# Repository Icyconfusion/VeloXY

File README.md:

# VeloXY
A CoreXY 3d printer with a heated chamber and bed. It has 300x300x320 print volume and 3 point bed-levelling. I made this project to be able to print higher quality materials. The printer runs Marlin firmware.

## **Assembly**
The assembly is centered around a frame made of galvanised square steel (40x40). The frame is essentially a cube, where the square steel is welded together, so no connectors are needed. Two cross bars at the top are lowered by ~60mm to provide clearance for the extruder and filament path. 

Components are mounted onto the square steel using rivet nuts. 

### Z axis

The Z axis uses 3 independent motors to enable 3 point bed-levelling. At each motor, there is a T8 leadscrew to drive motion, and an 8mm smooth rod for support. The smooth rod is press fit into the 3d printed brackets through small slits in the brackets for compliance. The nema 17 motor mounts to the bracket, and secures the leadscrew with a 5x8 shaft coupler. At the idler, the leadscrew is held in place with a 16x8x5 bearing, allowing rotation. 

The intersection of the corner Nema 17 motors with the square steel is not an error, as a section of the square steel will be cutout (a rectangle just bigger than the motor) so that the motor sits in there without touching any of the steel.

Bed supports hold an LM8UU bearing and a anti-backlash nut. This transfers motion to the bed. The bed sits on these supports through a threaded steel ball (Vcore system) which rests on metal dowels in the bracket.

### Gantry (X and Y)
The gantry is the 2020 T slot profile that moves back and forth along the Y axis. The gantry is supported by two 3d printed brackets, one at each end, that connect it to the MGN12H carriages. The Y linear rails are mounted on the underside of the frame.

 The gantry has a linear rail along the top face of the profile, this is the X axis.

The extruder runs along this linear rail for the X axis. The extruder is sat on a MGN12H carriage, and holds a nema 17 motor for the extruder and the hotend. Two blower fans cool the nozzle/part.

### Chamber
The chamber is mounted around the frame, aiming to create a closed off area that can be heated for better printing. The enclosure is made up of ACM, mounted on the top, back, bottom and sides using rivet nuts.

A hole is drilled in the back panel so that wires for electronics can enter the chamber.

The enclosure is finished with a polycarbonate door on a hinge mounted to the frame, with a 3d printed handle.

The chamber is heated by a PTC heater in the bottom corner, mounted to a base tube of square steel, and a vertical post using a small metal rectangle with mounting holes drilled.

### Motion
The printer is based on a coreXY motion system. The belts are stacked on top of each other, so there is no need for a crossover system.

There are pulleys on the idlers and belt post on the gantry. The belts connect to a post/screw on the extruder.

## **Electronics**
I designed a PCB motherboard around the mega2560 that will control the printer. The motherboard is 2 layers and uses A4988 footprint drivers. Power for the motors and heaters enters the board with a screw terminal from the 24v 600w PSU. There is also an 5v screw terminal input which powers the motor driver logic, lcd and if needed the arduino. The 5v comes from the psu but with a buck converter between. There is a third power input for the arduino vin pin which can be used if needed, but the arduino can also be powered by the 5v supply and usb. The LCD connects to a 4 pin header, with RX, TX, 5V and GND. All three heaters (Hotend, bed and chamber) are controlled through TO-220 mosfets, but the chamber has its own PSU. There are also fuses for the power inputs.

## **BOM**
**Printed parts**
| Part | Quantity | Picture |
|------|----------|---------|
| A bottom corner | 1 |
| A bed support | 1 | 
| A idler | 1 |
| A motor | 1 | 
| A gantry belt post | 1 |
| A gantry mount | 1 | 
| B bottom corner | 1 | 
| B bed support | 1 |
| B idler | 1 | 
| B motor | 1 | 
| B gantry belt post | 1 | 
| B gantry mount | 1 | 
| Z front bracket | 1 |
| Front bed support | 1 | 
| Front top support | 1 | 
| Handle | 1 | 
| Extruder | 1 | 
| Electronics case | 1 | 

**Purchased Parts**
|Name             |Purpose                                                                                                                                                                                                                                |Quantity|Total Cost (USD)|Link                                                                                                                                                                                                                                                                                                                                                                                                                                                                                                                                                                                                                                                                                                                                                                                   |Distributor       |
|-----------------|---------------------------------------------------------------------------------------------------------------------------------------------------------------------------------------------------------------------------------------|--------|----------------|---------------------------------------------------------------------------------------------------------------------------------------------------------------------------------------------------------------------------------------------------------------------------------------------------------------------------------------------------------------------------------------------------------------------------------------------------------------------------------------------------------------------------------------------------------------------------------------------------------------------------------------------------------------------------------------------------------------------------------------------------------------------------------------|------------------|
|Mosfets          |IRLB3034PBF MOSFETs for controlling the heaters of the printer.                                                                                                                                                                        |3       |4.06            |https://www.aliexpress.com/item/4000222160431.html?spm=a2g0o.productlist.main.1.701d2eacHI2noh&algo_pvid=e8668151-e46e-4309-800e-2077e72375df&algo_exp_id=e8668151-e46e-4309-800e-2077e72375df-0&pdp_ext_f=%7B%22order%22%3A%2266%22%2C%22spu_best_type%22%3A%22price%22%2C%22eval%22%3A%221%22%2C%22fromPage%22%3A%22search%22%7D&pdp_npi=6%40dis%21AUD%215.88%211.45%21%21%214.00%210.98%21%40210328c017752737169366011ebd3e%2110000000864172031%21sea%21AU%216973160092%21ABX%211%210%21n_tag%3A-29910%3Bd%3A6fbdfe4b%3Bm03_new_user%3A-29895%3BpisId%3A5000000197843419&curPageLogUid=LSIIE8dqceVT&utparam-url=scene%3Asearch%7Cquery_from%3A%7Cx_object_id%3A4000222160431%7C_p_origin_prod%3A                                                                                    |Aliexpress        |
|Capacitors       |220 uf 50V capacitors for the motherboard                                                                                                                                                                                              |6       |3.80            |https://www.aliexpress.com/item/1005011631970768.html?spm=a2g0o.productlist.main.6.11e01afbH7otWg&algo_pvid=ea0e70cf-552e-4c24-aa21-9a0a49e67bf6&algo_exp_id=ea0e70cf-552e-4c24-aa21-9a0a49e67bf6-5&pdp_ext_f=%7B%22order%22%3A%22889%22%2C%22eval%22%3A%221%22%2C%22fromPage%22%3A%22search%22%7D&pdp_npi=6%40dis%21AUD%212.71%211.45%21%21%2112.71%216.80%21%4021030a6217752717653413118ea4b9%2112000056427936714%21sea%21AU%216973160092%21ABX%211%210%21n_tag%3A-29910%3Bd%3A6fbdfe4b%3Bm03_new_user%3A-29895%3BpisId%3A5000000197843456&curPageLogUid=3mj5Ipi5ZoII&utparam-url=scene%3Asearch%7Cquery_from%3A%7Cx_object_id%3A1005011631970768%7C_p_origin_prod%3A                                                                                                                |Aliexpress        |
|female headers   |For connecting the A4988 drivers to the motherboard                                                                                                                                                                                    |12      |5.52            |https://www.aliexpress.com/item/4000059515638.html?spm=a2g0o.productlist.main.9.3a78pSyIpSyIFy&algo_pvid=1a6644c9-0d15-4e98-a974-f6610573b0b1&algo_exp_id=1a6644c9-0d15-4e98-a974-f6610573b0b1-8&pdp_ext_f=%7B%22order%22%3A%22284%22%2C%22eval%22%3A%221%22%2C%22fromPage%22%3A%22search%22%7D&pdp_npi=6%40dis%21AUD%2114.21%211.45%21%21%219.67%210.98%21%402101c44517752688612072065e0933%2112000028027640857%21sea%21AU%216973160092%21ABX%211%210%21n_tag%3A-29910%3Bd%3A6fbdfe4b%3Bm03_new_user%3A-29895%3BpisId%3A5000000197843419&curPageLogUid=7JxZIhsilBI0&utparam-url=scene%3Asearch%7Cquery_from%3A%7Cx_object_id%3A4000059515638%7C_p_origin_prod%3A                                                                                                                      |Aliexpress        |
|Male pin headers |For connecting components like endstops and the MCU to the motherboard                                                                                                                                                                 |1       |8.74            |https://www.aliexpress.com/item/1005011692961056.html?spm=a2g0o.productlist.main.6.57f6487bkxhM2t&algo_pvid=cf18d2a9-385d-4fc5-8ad6-75333b3f4af1&algo_exp_id=cf18d2a9-385d-4fc5-8ad6-75333b3f4af1-5&pdp_ext_f=%7B%22order%22%3A%221274%22%2C%22eval%22%3A%221%22%2C%22orig_sl_item_id%22%3A%221005011692961056%22%2C%22orig_item_id%22%3A%221005010337310648%22%2C%22fromPage%22%3A%22search%22%7D&pdp_npi=6%40dis%21AUD%217.68%211.45%21%21%2136.00%216.80%21%40210319b717752687310407356e8479%2112000056260706301%21sea%21AU%216973160092%21ABX%211%210%21n_tag%3A-29910%3Bd%3A6fbdfe4b%3Bm03_new_user%3A-29895%3BpisId%3A5000000197843456&curPageLogUid=2ZVKkz74AUod&utparam-url=scene%3Asearch%7Cquery_from%3A%7Cx_object_id%3A1005011692961056%7C_p_origin_prod%3A1005010337310648|Aliexpress        |
|Blower fan       |Cooling the nozzle/part                                                                                                                                                                                                                |2       |4.60            |https://www.aliexpress.com/item/1005006744255466.html?spm=a2g0o.productlist.main.18.7f9f5db3RONGTo&aem_p4p_detail=202604031902574206037527561500000981548&algo_pvid=619f652d-2eee-4128-aee8-e13ab89bcbb5&algo_exp_id=619f652d-2eee-4128-aee8-e13ab89bcbb5-15&pdp_ext_f=%7B%22order%22%3A%2233%22%2C%22eval%22%3A%221%22%2C%22fromPage%22%3A%22search%22%7D&pdp_npi=6%40dis%21AUD%216.67%216.29%21%21%2131.26%2129.48%21%402103274e17752681771328222e87ef%2112000056790491158%21sea%21AU%216973160092%21ABX%211%210%21n_tag%3A-29910%3Bd%3A6fbdfe4b%3Bm03_new_user%3A-29895&curPageLogUid=7c9OwehxviKo&utparam-url=scene%3Asearch%7Cquery_from%3A%7Cx_object_id%3A1005006744255466%7C_p_origin_prod%3A&search_p4p_id=202604031902574206037527561500000981548_4                          |Aliexpress        |
|Bearing          |16x8x5 bearing for holding the top of leadscrews in place                                                                                                                                                                              |3       |0.45            |https://jlcmc.com/product/b/C15/BR8364/deep-groove-ball-bearing-double-side-with-dust-cover                                                                                                                                                                                                                                                                                                                                                                                                                                                                                                                                                                                                                                                                                            |JLCMC             |
|Fuse             |KCD3 Fuse holder for the motherboard. For the main PSU, 30-35A fuse. For bed PSU, 20A fuse.                                                                                                                                            |2       |7.80            |https://www.aliexpress.com/item/1005005182079397.html?spm=a2g0o.productlist.main.37.46d42d7bflqGAT&algo_pvid=e277db1d-0a25-4cd8-b4e5-8a226238a0aa&algo_exp_id=e277db1d-0a25-4cd8-b4e5-8a226238a0aa-36&pdp_ext_f=%7B%22order%22%3A%22680%22%2C%22eval%22%3A%221%22%2C%22fromPage%22%3A%22search%22%7D&pdp_npi=6%40dis%21AUD%215.28%211.45%21%21%2124.76%216.81%21%402101e2b017752723764397683ed113%2112000040889150142%21sea%21AU%216973160092%21ABX%211%210%21n_tag%3A-29910%3Bd%3A6fbdfe4b%3Bm03_new_user%3A-29895%3BpisId%3A5000000197843456&curPageLogUid=zcssCcAWRYTf&utparam-url=scene%3Asearch%7Cquery_from%3A%7Cx_object_id%3A1005005182079397%7C_p_origin_prod%3A                                                                                                              |Aliexpress        |
|Screw terminals  |30A Screw terminals for powering motherboard, and connecting heaters to motherboard                                                                                                                                                    |7       |5.52            |https://www.aliexpress.com/item/1005009941526260.html?spm=a2g0o.productlist.main.11.6699aRudaRudhq&algo_pvid=89ec62cf-593d-44c2-9882-a10513144a1b&algo_exp_id=89ec62cf-593d-44c2-9882-a10513144a1b-10&pdp_ext_f=%7B%22order%22%3A%229%22%2C%22eval%22%3A%221%22%2C%22fromPage%22%3A%22search%22%7D&pdp_npi=6%40dis%21AUD%213.72%212.53%21%21%2117.41%2111.84%21%402101eecd17752720149076217e3ec5%2112000050638072357%21sea%21AU%216973160092%21ABX%211%210%21n_tag%3A-29910%3Bd%3A6fbdfe4b%3Bm03_new_user%3A-29895&curPageLogUid=gSVVO5LFxt8p&utparam-url=scene%3Asearch%7Cquery_from%3A%7Cx_object_id%3A1005009941526260%7C_p_origin_prod%3A                                                                                                                                          |Aliexpress        |
|Resistors        |1/4 watt, 10k and 150 ohm resistors for the motherboard MOSFETS                                                                                                                                                                        |6       |5.73            |https://www.aliexpress.com/item/1005008464765307.html?spm=a2g0o.productlist.main.3.6beeb7seb7se95&algo_pvid=9d5a656c-2e93-448e-8bdb-5524d68c3fdc&algo_exp_id=9d5a656c-2e93-448e-8bdb-5524d68c3fdc-2&pdp_ext_f=%7B%22order%22%3A%2233%22%2C%22eval%22%3A%221%22%2C%22fromPage%22%3A%22search%22%7D&pdp_npi=6%40dis%21AUD%214.14%214.14%21%21%2119.41%2119.41%21%40210319b717752734548065346e842d%2112000045251572444%21sea%21AU%216973160092%21ABX%211%210%21n_tag%3A-29910%3Bd%3A6fbdfe4b%3Bm03_new_user%3A-29895&curPageLogUid=tQ7l9CIgVT6O&utparam-url=scene%3Asearch%7Cquery_from%3A%7Cx_object_id%3A1005008464765307%7C_p_origin_prod%3A                                                                                                                                           |Aliexpress        |
|Capacitors       |100 nf (0.1 uf) 50V ceramic capacitors for the motherboard                                                                                                                                                                             |6       |0.00            |https://www.aliexpress.com/item/1005006883576409.html?spm=a2g0o.productlist.main.33.49e251a9tTNOzG&algo_pvid=c24414d9-97ff-45ec-b095-ba25d4c4afb2&algo_exp_id=c24414d9-97ff-45ec-b095-ba25d4c4afb2-30&pdp_ext_f=%7B%22order%22%3A%22101%22%2C%22eval%22%3A%221%22%2C%22fromPage%22%3A%22search%22%7D&pdp_npi=6%40dis%21AUD%213.33%213.20%21%21%2115.59%2114.97%21%402101e62517752716206776129e0a0b%2112000038613636397%21sea%21AU%216973160092%21ABX%211%210%21n_tag%3A-29910%3Bd%3A6fbdfe4b%3Bm03_new_user%3A-29895&curPageLogUid=jVSqGQnLf0eX&utparam-url=scene%3Asearch%7Cquery_from%3A%7Cx_object_id%3A1005006883576409%7C_p_origin_prod%3A                                                                                                                                        |Aliexpress        |
|Screws           |For fastening components to the the rivet nuts. 225 M5, 5 M4, 100 M3                                                                                                                                                                   |330     |7.73            |https://jlcmc.com/product/s/E02/EDLA/hex-socket-screw-full-partial-thread-standard-type-(din-912-gb-t-70.1)                                                                                                                                                                                                                                                                                                                                                                                                                                                                                                                                                                                                                                                                            |JLCMC             |
|PEI sheet        |The print surface that goes on top of the print bed. 310x310                                                                                                                                                                           |1       |14.63           |https://www.aliexpress.com/item/1005006866749353.html?spm=a2g0o.productlist.main.17.7784qUMIqUMIYV&algo_pvid=93b61df2-3243-437c-82de-90710947c82e&algo_exp_id=93b61df2-3243-437c-82de-90710947c82e-16&pdp_ext_f=%7B%22order%22%3A%221253%22%2C%22eval%22%3A%221%22%2C%22fromPage%22%3A%22search%22%7D&pdp_npi=6%40dis%21AUD%2112.09%211.45%21%21%2156.65%216.79%21%402101e2b417752670140866859eb963%2112000051559315778%21sea%21AU%216973160092%21ABX%211%210%21n_tag%3A-29910%3Bd%3A6fbdfe4b%3Bm03_new_user%3A-29895%3BpisId%3A5000000197843419&curPageLogUid=riy6tkaUbw0i&utparam-url=scene%3Asearch%7Cquery_from%3A%7Cx_object_id%3A1005006866749353%7C_p_origin_prod%3A                                                                                                            |Aliexpress        |
|Polycarbonate    |Polycarbonate sheet for the door.                                                                                                                                                                                                      |1       |30.00           |https://www.bunnings.com.au/suntuf-400-x-400-x-8mm-clear-palsun-polycarbonate-sheet-8mm_p1010483                                                                                                                                                                                                                                                                                                                                                                                                                                                                                                                                                                                                                                                                                       |Bunnings          |
|Heat set inserts |Attaching electronics case lid                                                                                                                                                                                                         |4       |0.17            |https://jlcmc.com/product/s/E04/EMLU/insert-nut-through-hole                                                                                                                                                                                                                                                                                                                                                                                                                                                                                                                                                                                                                                                                                                                           |JLCMC             |
|Rivet nuts       |Nuts for fastening things to the square steel tubing. Need 175 M5, 5 M4, 100 M3                                                                                                                                                        |280     |7.59            |https://jlcmc.com/product/s/E12/EMJE/rivet-nut-pull-through-ribbed-dome-head                                                                                                                                                                                                                                                                                                                                                                                                                                                                                                                                                                                                                                                                                                           |JLCMC             |
|MK8 extruder     |The MK8 extruder pushes filament into the hotend using the Nema 17 motor                                                                                                                                                               |1       |4.33            |https://www.aliexpress.com/item/1005007542803374.html?spm=a2g0o.productlist.main.30.4871298e6622Ky&algo_pvid=c56a8ecb-e1aa-4c08-83e4-934475fec138&algo_exp_id=c56a8ecb-e1aa-4c08-83e4-934475fec138-29&pdp_ext_f=%7B%22order%22%3A%22642%22%2C%22spu_best_type%22%3A%22price%22%2C%22eval%22%3A%221%22%2C%22fromPage%22%3A%22search%22%7D&pdp_npi=6%40dis%21AUD%216.64%211.45%21%21%214.52%210.99%21%402103212317752660219846218e3305%2112000041225614025%21sea%21AU%216973160092%21ABX%211%210%21n_tag%3A-29910%3Bd%3A6fbdfe4b%3Bm03_new_user%3A-29895%3BpisId%3A5000000197843419&curPageLogUid=lLozSRLeO441&utparam-url=scene%3Asearch%7Cquery_from%3A%7Cx_object_id%3A1005007542803374%7C_p_origin_prod%3A                                                                           |Aliexpress        |
|PTC heater       |The space heater for the heated chamber of the printer to enable printing harder materials. 24v 400w.                                                                                                                                  |1       |17.00           |https://www.aliexpress.com/item/1005007442989854.html?spm=a2g0o.productlist.main.1.71f3a8d0sZSDY&algo_pvid=2ed4a76d-82cf-48c9-8808-acc357ff1653&algo_exp_id=2ed4a76d-82cf-48c9-8808-acc357ff1653-0&pdp_ext_f=%7B%22order%22%3A%224885%22%2C%22spu_best_type%22%3A%22price%22%2C%22eval%22%3A%221%22%2C%22fromPage%22%3A%22search%22%7D&pdp_npi=6%40dis%21AUD%2116.43%215.96%21%21%2111.09%214.02%21%402103212517748608234258144e3112%2112000040774614547%21sea%21AU%216973160092%21ABX%211%210%21n_tag%3A-29910%3Bd%3A6fbdfe4b%3Bm03_new_user%3A-29895%3BpisId%3A5000000197827888&curPageLogUid=vXhUvAlolt2a&utparam-url=scene%3Asearch%7Cquery_from%3A%7Cx_object_id%3A1005007442989854%7C_p_origin_prod%3A                                                                           |Aliexpress        |
|Heated bed       |300x300 24v heated bed to heat up the print surface                                                                                                                                                                                    |1       |25.00           |https://www.aliexpress.com/item/1005008233590835.html?spm=a2g0o.productlist.main.9.35cb6ab01pwLms&algo_pvid=a5394779-b4a1-40e8-9eea-16bd6e430344&algo_exp_id=a5394779-b4a1-40e8-9eea-16bd6e430344-8&pdp_ext_f=%7B%22order%22%3A%2298%22%2C%22eval%22%3A%221%22%2C%22fromPage%22%3A%22search%22%7D&pdp_npi=6%40dis%21AUD%2118.09%2118.09%21%21%2184.53%2184.53%21%40210319b717748605717518699e414c%2112000044318998456%21sea%21AU%216973160092%21ABX%211%210%21n_tag%3A-29910%3Bd%3A6fbdfe4b%3Bm03_new_user%3A-29895&curPageLogUid=EuYcYv5fmPI0&utparam-url=scene%3Asearch%7Cquery_from%3A%7Cx_object_id%3A1005008233590835%7C_p_origin_prod%3A                                                                                                                                         |Aliexpress        |
|Square steel tube|2mm thick 40x40 Galvanised square steel tubing is the frame for the printer. I will use 40x40 as it has greater strength. I will cut it to length, drill holes where necessary for mounting and then weld together. I will need 6m.    |1       |31.06           |https://www.rhssteelsupplies.com.au/hikashop-menu-for-categories-listing/product/3127-galvanised-square-hollow-box-section-40-x-40-x-2-5-gal-8-metres.html                                                                                                                                                                                                                                                                                                                                                                                                                                                                                                                                                                                                                             |RHS Steel Supplies|
|ACM panel        |ACM panel will make the enclosure for the printer. I need to use ACM as it is the cheapest suitable material, as it must be able to contain the heat of the chamber without weakening. I will cut/bend the ACM to fit around the frame.|1       |60.00           |https://plastix.com.au/product/aluminium-composite-panels/?attribute_pa_acp-colours=white-gloss-primer&attribute_pa_size=full-sheet-2440-x-1220mm-8x4                                                                                                                                                                                                                                                                                                                                                                                                                                                                                                                                                                                                                                  |Plastix.com.au    |

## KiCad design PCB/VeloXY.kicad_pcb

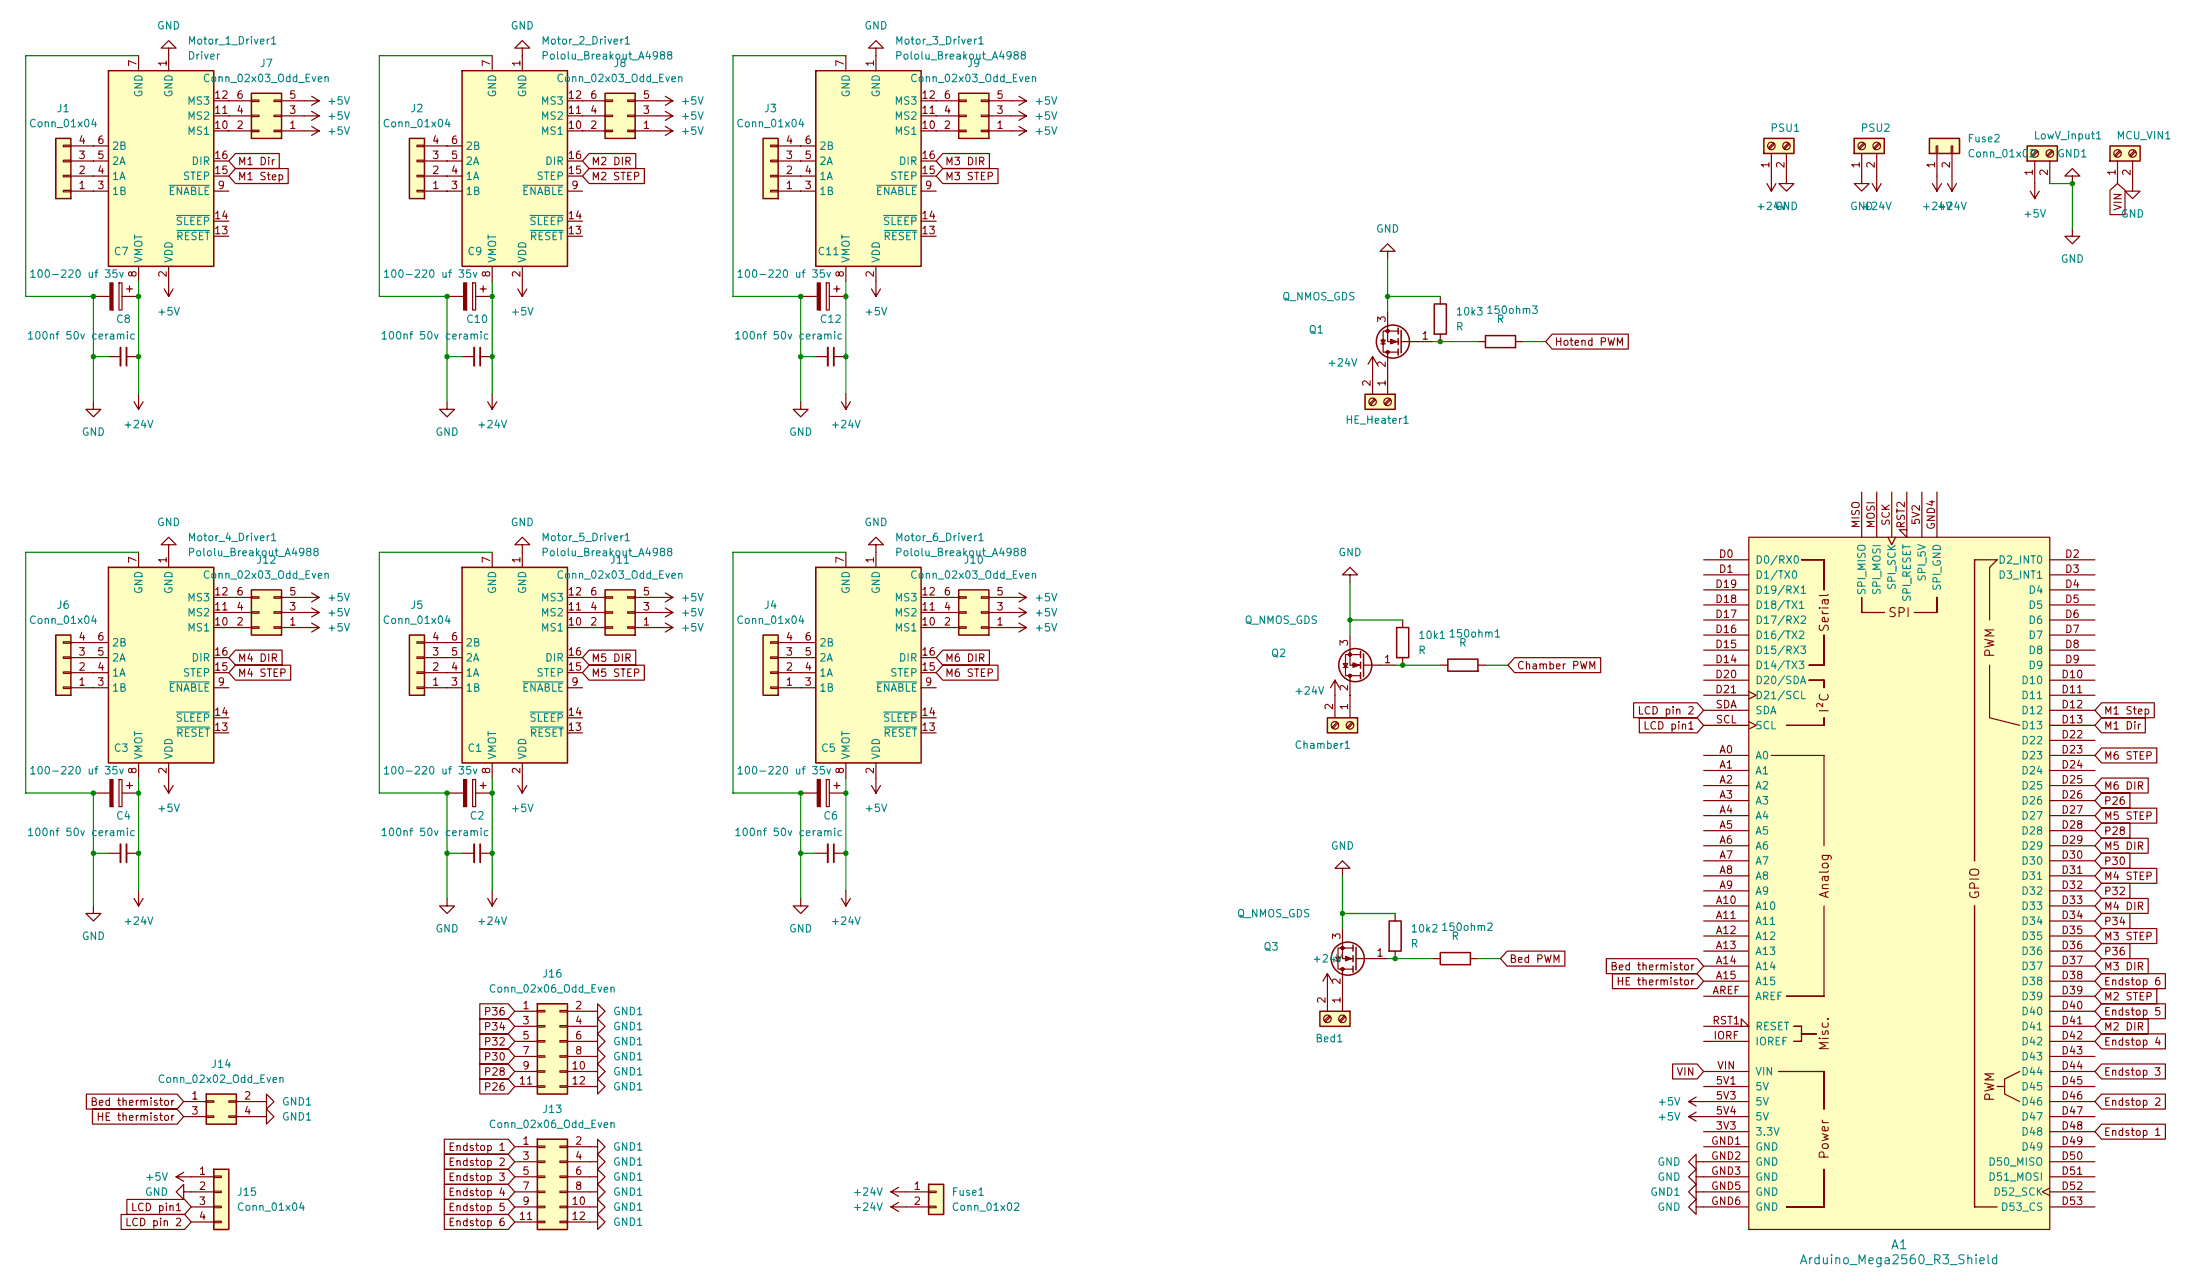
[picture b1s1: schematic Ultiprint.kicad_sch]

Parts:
10k1, 10k2, 10k3, 150ohm1, 150ohm2, 150ohm3: R; R_Axial_DIN0207_L6.3mm_D2.5mm_P7.62mm_Horizontal
A1: Arduino_Mega2560_R3_Shield
Bed1: Screw_Terminal_01x02; Wuerth_691311400102_P7.62mm
C1, C3, C5, C7, C9, C11: 100-220 uf 35v; CP_Radial_D8.0mm_P5.00mm
C2, C4, C6, C8, C10, C12: 100nf 50v ceramic; C_Disc_D5.0mm_W2.5mm_P5.00mm
Chamber1: Screw_Terminal_01x02; Wuerth_691311400102_P7.62mm
Fuse1, Fuse2: Conn_01x02; Fuse_Holder_KCD3_Medium
HE_Heater1: Screw_Terminal_01x02; Wuerth_691311400102_P7.62mm
J1, J2, J3, J4, J5, J6, J15: Conn_01x04; PinHeader_1x04_P2.54mm_Vertical
J7, J8, J9, J10, J11, J12: Conn_02x03_Odd_Even; PinHeader_2x03_P2.54mm_Vertical
J13, J16: Conn_02x06_Odd_Even; PinHeader_2x06_P2.54mm_Vertical
J14: Conn_02x02_Odd_Even; PinHeader_2x02_P2.54mm_Vertical
LowV_input1: Screw_Terminal_01x02; Wuerth_691311400102_P7.62mm
MCU_VIN1: Screw_Terminal_01x02; Wuerth_691311400102_P7.62mm
Motor_1_Driver1: Driver; Pololu_Breakout-16_15.2x20.3mm
Motor_2_Driver1, Motor_3_Driver1, Motor_4_Driver1, Motor_5_Driver1, Motor_6_Driver1: Pololu_Breakout_A4988; Pololu_Breakout-16_15.2x20.3mm
PSU1, PSU2: Screw_Terminal_01x02; Wuerth_691311400102_P7.62mm
Q1, Q2, Q3: Q_NMOS_GDS; TO-220-3_Vertical

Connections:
+5V: A1.5V3 (5V), A1.5V4 (5V), J7.1, J7.3, J7.5, J8.1, J8.3, J8.5, J9.1, J9.3, J9.5, J10.1, J10.3, J10.5, J11.1, J11.3, J11.5, J12.1, J12.3, J12.5, J15.1, LowV_input1.1, Motor_1_Driver1.2 (VDD), Motor_2_Driver1.2 (VDD), Motor_3_Driver1.2 (VDD), Motor_4_Driver1.2 (VDD), Motor_5_Driver1.2 (VDD), Motor_6_Driver1.2 (VDD)
+24V: Bed1.2, C1.1, C2.1, C3.1, C4.1, C5.1, C6.1, C7.1, C8.1, C9.1, C10.1, C11.1, C12.1, Chamber1.2, Fuse1.1, Fuse1.2, Fuse2.1, Fuse2.2, HE_Heater1.2, Motor_1_Driver1.8 (VMOT), Motor_2_Driver1.8 (VMOT), Motor_3_Driver1.8 (VMOT), Motor_4_Driver1.8 (VMOT), Motor_5_Driver1.8 (VMOT), Motor_6_Driver1.8 (VMOT), PSU1.1, PSU2.2
Bed PWM: 150ohm2.2
Bed thermistor: A1.A14, J14.1
Chamber PWM: 150ohm1.2
Endstop 1: A1.D48, J13.1
Endstop 2: A1.D46, J13.3
Endstop 3: A1.D44, J13.5
Endstop 4: A1.D42, J13.7
Endstop 5: A1.D40, J13.9
Endstop 6: A1.D38, J13.11
GND: 10k1.1, 10k2.1, 10k3.1, A1.GND2 (GND), A1.GND3 (GND), A1.GND5 (GND), A1.GND6 (GND), C1.2, C2.2, C3.2, C4.2, C5.2, C6.2, C7.2, C8.2, C9.2, C10.2, C11.2, C12.2, J13.2, J13.4, J13.6, J13.8, J13.10, J13.12, J14.2, J14.4, J15.2, J16.2, J16.4, J16.6, J16.8, J16.10, J16.12, LowV_input1.2, MCU_VIN1.2, Motor_1_Driver1.1 (GND), Motor_1_Driver1.7 (GND), Motor_2_Driver1.1 (GND), Motor_2_Driver1.7 (GND), Motor_3_Driver1.1 (GND), Motor_3_Driver1.7 (GND), Motor_4_Driver1.1 (GND), Motor_4_Driver1.7 (GND), Motor_5_Driver1.1 (GND), Motor_5_Driver1.7 (GND), Motor_6_Driver1.1 (GND), Motor_6_Driver1.7 (GND), PSU1.2, PSU2.1, Q1.3 (S), Q2.3 (S), Q3.3 (S)
HE thermistor: A1.A15, J14.3
Hotend PWM: 150ohm3.2
LCD pin1: A1.SCL, J15.3
LCD pin 2: A1.SDA, J15.4
M1 Dir: A1.D13, Motor_1_Driver1.16 (DIR)
M1 Step: A1.D12, Motor_1_Driver1.15 (STEP)
M2 DIR: A1.D41, Motor_2_Driver1.16 (DIR)
M2 STEP: A1.D39, Motor_2_Driver1.15 (STEP)
M3 DIR: A1.D37, Motor_3_Driver1.16 (DIR)
M3 STEP: A1.D35, Motor_3_Driver1.15 (STEP)
M4 DIR: A1.D33, Motor_4_Driver1.16 (DIR)
M4 STEP: A1.D31, Motor_4_Driver1.15 (STEP)
M5 DIR: A1.D29, Motor_5_Driver1.16 (DIR)
M5 STEP: A1.D27, Motor_5_Driver1.15 (STEP)
M6 DIR: A1.D25, Motor_6_Driver1.16 (DIR)
M6 STEP: A1.D23, Motor_6_Driver1.15 (STEP)
unnamed: Bed1.1, Q3.2 (D)
unnamed: Chamber1.1, Q2.2 (D)
unnamed: HE_Heater1.1, Q1.2 (D)
unnamed: J1.1, Motor_1_Driver1.3 (1B)
unnamed: J1.2, Motor_1_Driver1.4 (1A)
unnamed: J1.3, Motor_1_Driver1.5 (2A)
unnamed: J1.4, Motor_1_Driver1.6 (2B)
unnamed: J2.1, Motor_2_Driver1.3 (1B)
unnamed: J2.2, Motor_2_Driver1.4 (1A)
unnamed: J2.3, Motor_2_Driver1.5 (2A)
unnamed: J2.4, Motor_2_Driver1.6 (2B)
unnamed: J3.1, Motor_3_Driver1.3 (1B)
unnamed: J3.2, Motor_3_Driver1.4 (1A)
unnamed: J3.3, Motor_3_Driver1.5 (2A)
unnamed: J3.4, Motor_3_Driver1.6 (2B)
unnamed: J4.1, Motor_6_Driver1.3 (1B)
unnamed: J4.2, Motor_6_Driver1.4 (1A)
unnamed: J4.3, Motor_6_Driver1.5 (2A)
unnamed: J4.4, Motor_6_Driver1.6 (2B)
unnamed: J5.1, Motor_5_Driver1.3 (1B)
unnamed: J5.2, Motor_5_Driver1.4 (1A)
unnamed: J5.3, Motor_5_Driver1.5 (2A)
unnamed: J5.4, Motor_5_Driver1.6 (2B)
unnamed: J6.1, Motor_4_Driver1.3 (1B)
unnamed: J6.2, Motor_4_Driver1.4 (1A)
unnamed: J6.3, Motor_4_Driver1.5 (2A)
unnamed: J6.4, Motor_4_Driver1.6 (2B)
unnamed: J7.2, Motor_1_Driver1.10 (MS1)
unnamed: J7.4, Motor_1_Driver1.11 (MS2)
unnamed: J7.6, Motor_1_Driver1.12 (MS3)
unnamed: J8.2, Motor_2_Driver1.10 (MS1)
unnamed: J8.4, Motor_2_Driver1.11 (MS2)
unnamed: J8.6, Motor_2_Driver1.12 (MS3)
unnamed: J9.2, Motor_3_Driver1.10 (MS1)
unnamed: J9.4, Motor_3_Driver1.11 (MS2)
unnamed: J9.6, Motor_3_Driver1.12 (MS3)
unnamed: J10.2, Motor_6_Driver1.10 (MS1)
unnamed: J10.4, Motor_6_Driver1.11 (MS2)
unnamed: J10.6, Motor_6_Driver1.12 (MS3)
unnamed: J11.2, Motor_5_Driver1.10 (MS1)
unnamed: J11.4, Motor_5_Driver1.11 (MS2)
unnamed: J11.6, Motor_5_Driver1.12 (MS3)
unnamed: J12.2, Motor_4_Driver1.10 (MS1)
unnamed: J12.4, Motor_4_Driver1.11 (MS2)
unnamed: J12.6, Motor_4_Driver1.12 (MS3)
unnamed: 10k3.2, 150ohm3.1, Q1.1 (G)
unnamed: 10k1.2, 150ohm1.1, Q2.1 (G)
unnamed: 10k2.2, 150ohm2.1, Q3.1 (G)
P26: A1.D26, J16.11
P28: A1.D28, J16.9
P30: A1.D30, J16.7
P32: A1.D32, J16.5
P34: A1.D34, J16.3
P36: A1.D36, J16.1
VIN: A1.VIN, MCU_VIN1.1

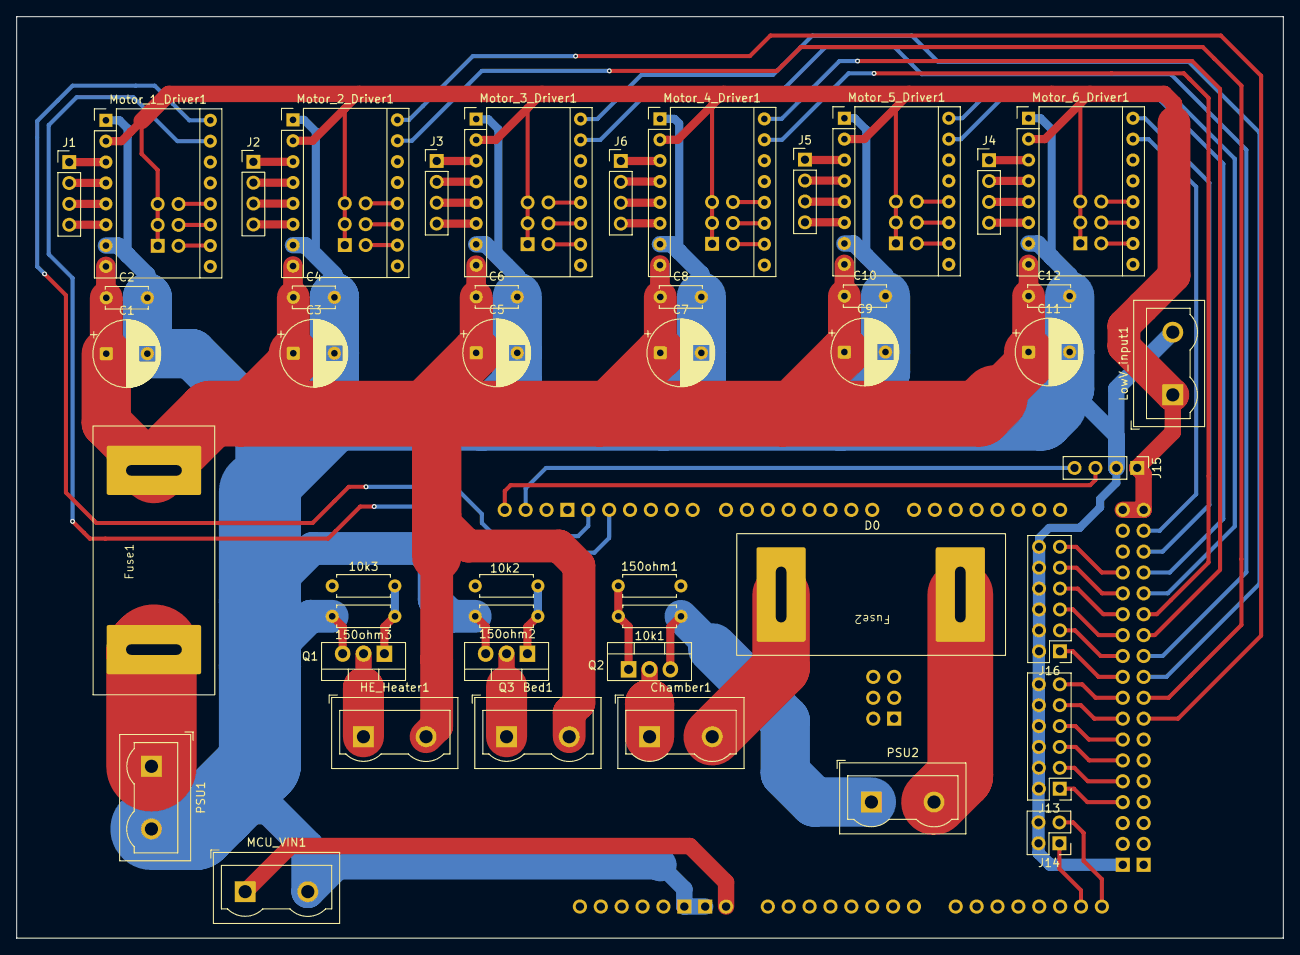
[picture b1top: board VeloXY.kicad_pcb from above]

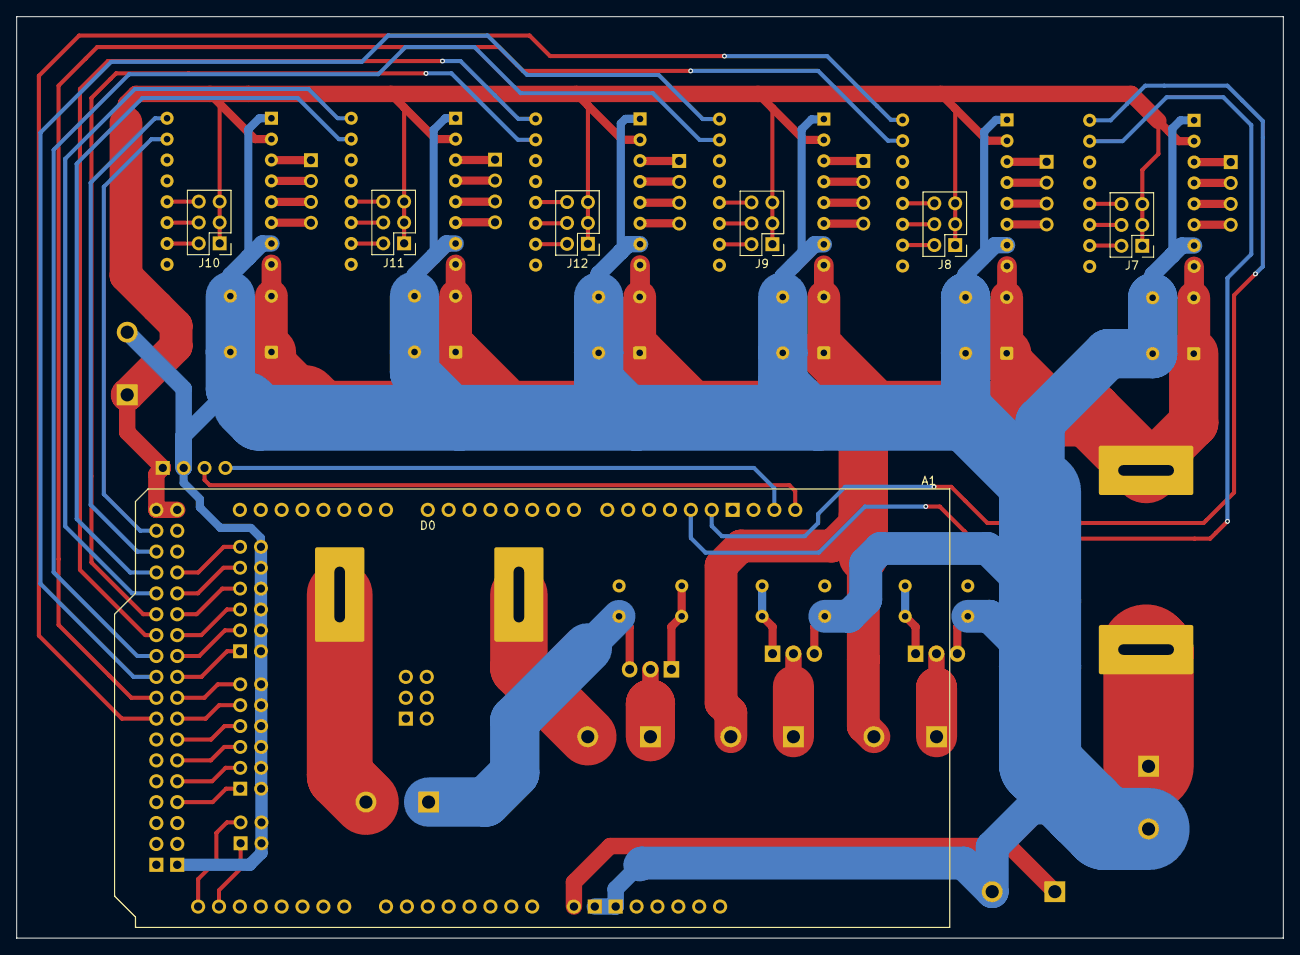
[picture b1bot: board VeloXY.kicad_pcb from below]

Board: 2 copper layers, 154.1 x 112.1 mm, 53 parts (6 on the bottom side), 80 nets.

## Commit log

2026-04-03 Rename Ultiprint.kicad_pcb to PCB/VeloXY.kicad_pcb
2026-04-03 Rename Ultiprint.kicad_prl to PCB/VeloXY.kicad_prl
2026-04-03 Rename Ultiprint.kicad_pro to PCB/VeloXY.kicad_pro
2026-04-03 Rename Ultiprint.kicad_sch to PCB/VeloXY.kicad_sch
2026-04-03 Create e
2026-04-03 Rename Configuration.h to Firmware/Configuration.h
2026-04-03 Rename Configuration_adv.h to Firmware/Configuration_adv.h
2026-04-03 Rename Marlin.zip to Firmware/Marlin.zip
2026-04-03 Rename config.ini to firmwareconfig.ini
2026-04-03 Rename firmwareconfig.ini to Firmware/config.ini
2026-04-05 Rename A+bed+support.stp to CAD/A+bed+support.stp
2026-04-05 Rename A+corner+bracket.stp to CAD/A+corner+bracket.stp
2026-04-05 Rename A+idler.stp to CAD/A+idler.stp
2026-04-05 Rename A+motor.stp to CAD/A+motor.stp
2026-04-05 Rename Assembly (1).stp to CAD/Assembly (1).stp
2026-04-05 Rename B+bed+support+new.stp to CAD/B+bed+support+new.stp
2026-04-05 Rename B+corner+bracket.stp to CAD/B+corner+bracket.stp
2026-04-05 Rename B+idler.stp to CAD/B+idler.stp
2026-04-05 Rename B+motor.stp to CAD/B+motor.stp
2026-04-05 Rename Bed+support+rear.stp to CAD/Bed+support+rear.stp
2026-04-05 Rename Electronics+case.stp to CAD/Electronics+case.stp
2026-04-05 Rename Front+top+support.stp to CAD/Front+top+support.stp
2026-04-05 Rename Gantry+belt+post+B.stp to CAD/Gantry+belt+post+B.stp
2026-04-05 Rename Gantry+belt+post.stp to CAD/Gantry+belt+post.stp
2026-04-05 Rename Handle.stp to CAD/Handle.stp
2026-04-05 Rename X+carriage.stp to CAD/X+carriage.stp
2026-04-05 Rename Y+carriage+A.stp to CAD/Y+carriage+A.stp
2026-04-05 Rename Y+carriage+B.stp to CAD/Y+carriage+B.stp
2026-04-05 Rename Z+front+bracket.stp to CAD/Z+front+bracket.stp
